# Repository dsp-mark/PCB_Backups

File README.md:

# PCB Storage

Storing KiCAD PCBs here for backup just in case something goes wrong on KiCAD or I need to work on a different computer.

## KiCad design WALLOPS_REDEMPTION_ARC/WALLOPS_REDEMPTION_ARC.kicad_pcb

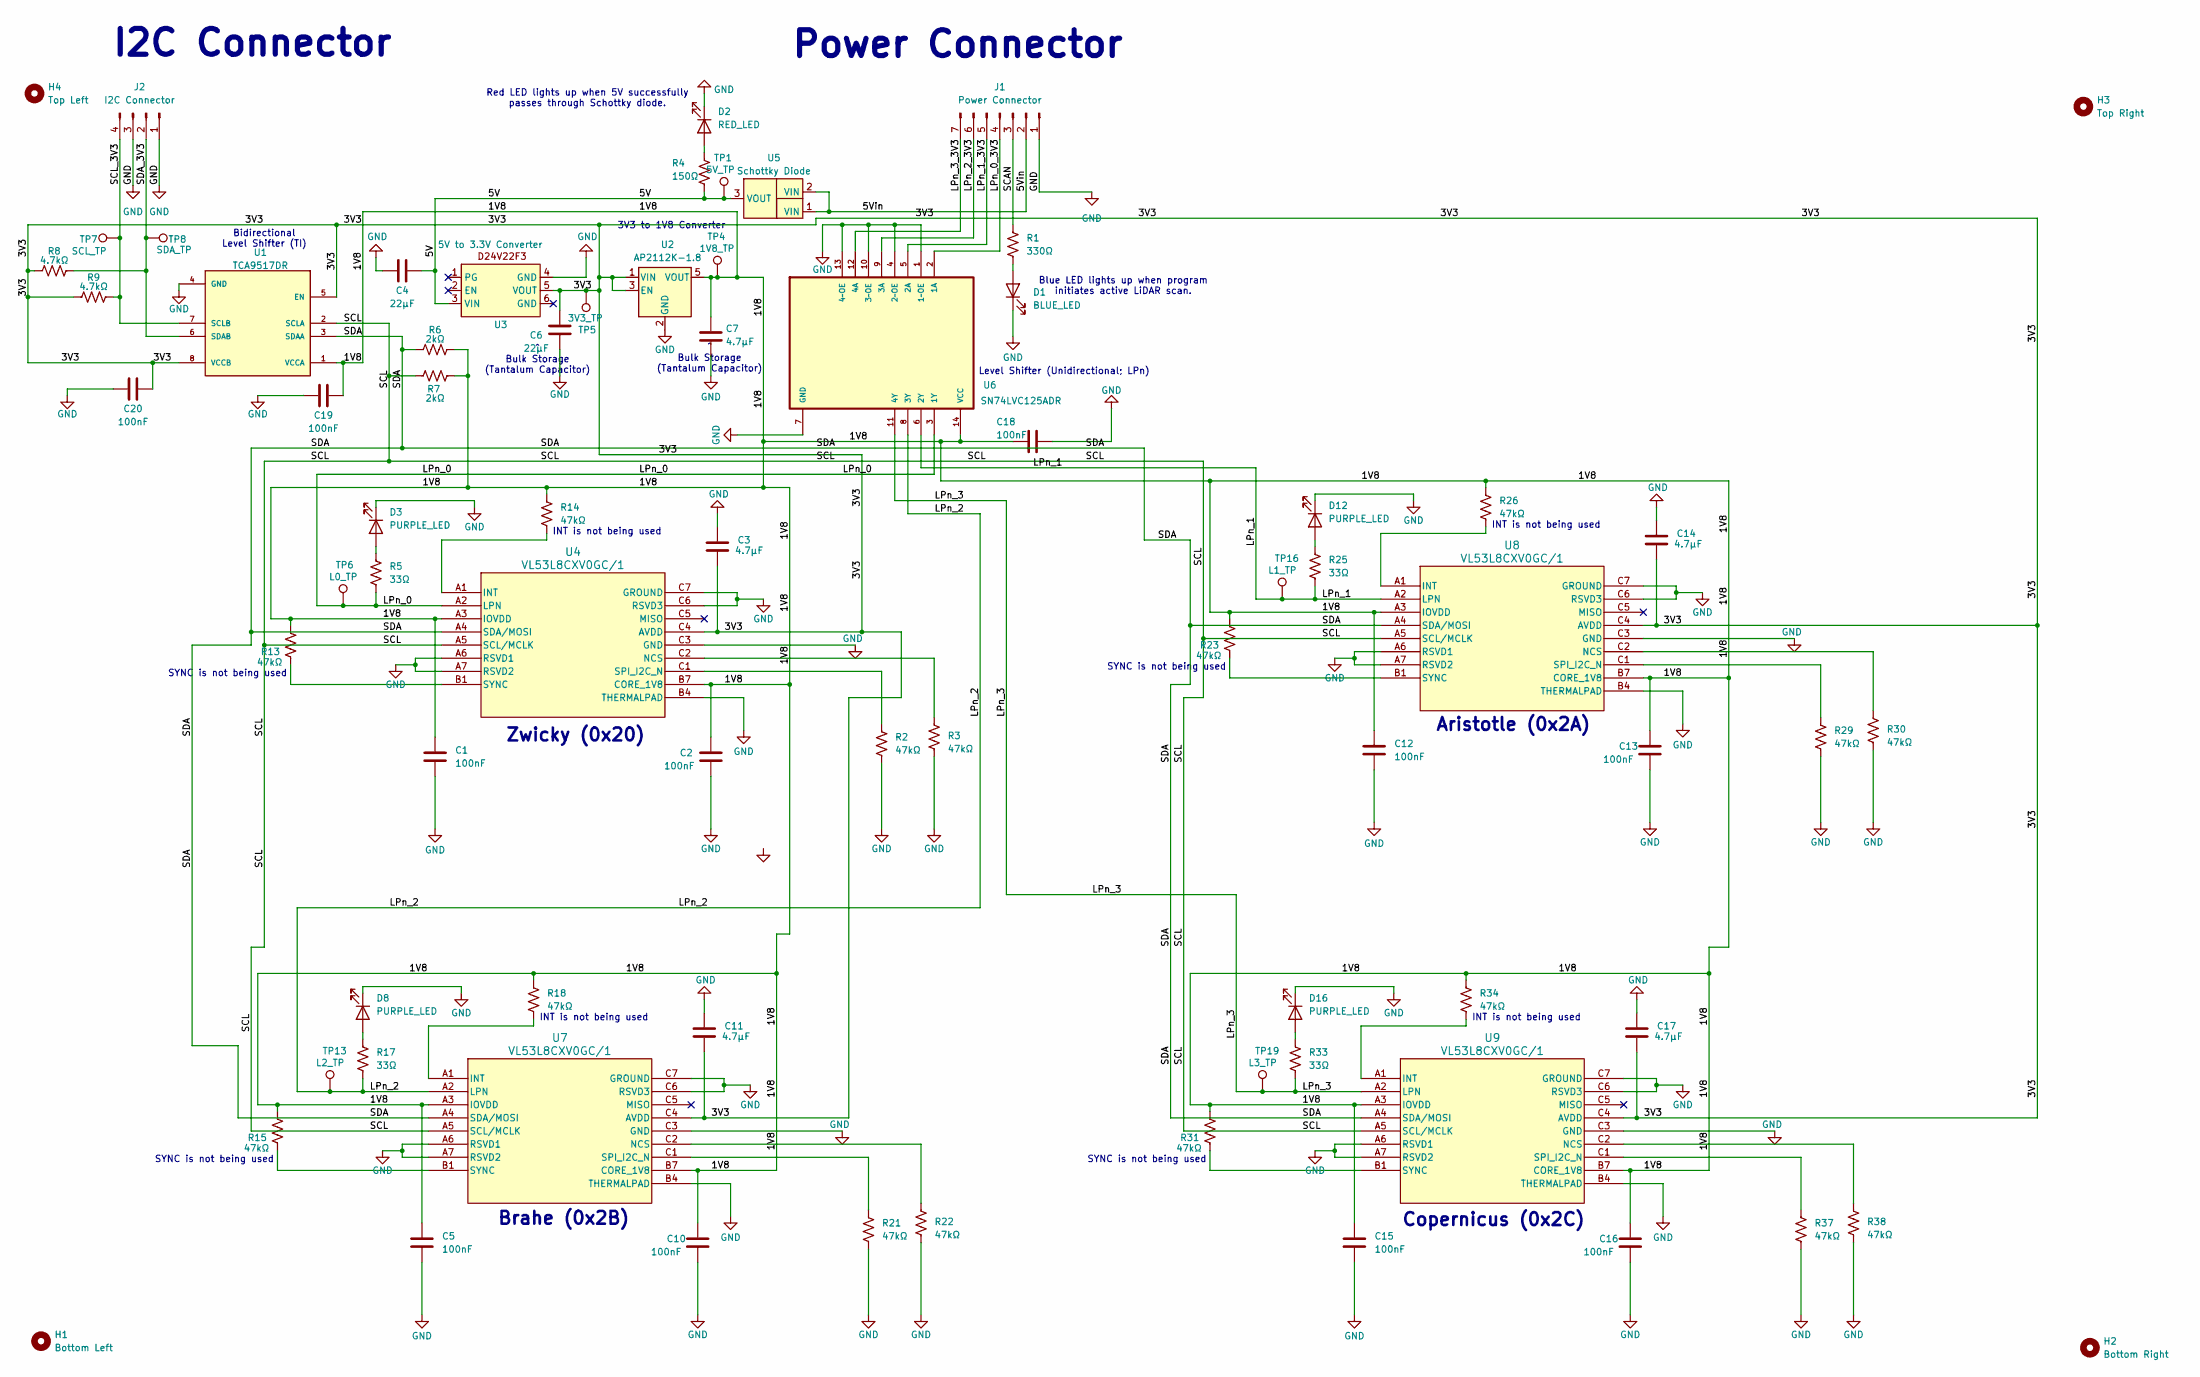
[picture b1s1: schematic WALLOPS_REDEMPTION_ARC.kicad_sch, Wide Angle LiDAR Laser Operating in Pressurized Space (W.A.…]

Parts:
C1, C2, C5, C10, C12, C13, C15, C16, C18, C19, C20: 100nF; C_0805_2012Metric_Pad1.18x1.45mm_HandSolder
C3, C7, C11, C14, C17: 4.7μF; C_0805_2012Metric_Pad1.18x1.45mm_HandSolder
C4, C6: 22μF; C_0805_2012Metric_Pad1.18x1.45mm_HandSolder
D1: BLUE_LED; LED_0805_2012Metric_Pad1.15x1.40mm_HandSolder
D2: RED_LED; LED_0805_2012Metric_Pad1.15x1.40mm_HandSolder
D3, D8, D12, D16: PURPLE_LED; LED_0805_2012Metric_Pad1.15x1.40mm_HandSolder
H1: Bottom Left; MountingHole_3.2mm_M3
H2: Bottom Right; MountingHole_3.2mm_M3
H3: Top Right; MountingHole_3.2mm_M3
H4: Top Left; MountingHole_3.2mm_M3
J1: Power Connector; JST_PH_S7B-PH-K_1x07_P2.00mm_Horizontal
J2: I2C Connector; JST_PH_S4B-PH-K_1x04_P2.00mm_Horizontal
R1: 330Ω; R_0805_2012Metric_Pad1.20x1.40mm_HandSolder
R2, R3, R13, R14, R15, R18, R21, R22, R23, R26, R29, R30, R31, R34, R37, R38: 47kΩ; R_0805_2012Metric_Pad1.20x1.40mm_HandSolder
R4: 150Ω; R_0805_2012Metric_Pad1.20x1.40mm_HandSolder
R5, R17, R25, R33: 33Ω; R_0805_2012Metric_Pad1.20x1.40mm_HandSolder
R6, R7: 2kΩ; R_0805_2012Metric_Pad1.20x1.40mm_HandSolder
R8, R9: 4.7kΩ; R_0805_2012Metric_Pad1.20x1.40mm_HandSolder
TP1: 5V_TP; TestPoint_Pad_D1.0mm
TP4: 1V8_TP; TestPoint_Pad_D1.0mm
TP5: 3V3_TP; TestPoint_Pad_D1.0mm
TP6: L0_TP; TestPoint_Pad_D1.0mm
TP7: SCL_TP; TestPoint_Pad_D1.0mm
TP8: SDA_TP; TestPoint_Pad_D1.0mm
TP13: L2_TP; TestPoint_Pad_D1.0mm
TP16: L1_TP; TestPoint_Pad_D1.0mm
TP19: L3_TP; TestPoint_Pad_D1.0mm
U1: TCA9517DR; SOIC127P599X175-8N; PARTREV D
U2: AP2112K-1.8; SOT-23-5
U3: 5V to 3.3V Converter; D24V22F3
U4, U7, U8, U9: VL53L8CXV0GC/1; vl53l8cx_smd
U5: Schottky Diode; TO-277B
U6: SN74LVC125ADR; SOIC127P600X175-14N

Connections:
/1V8: C1.1, C2.1, C5.1, C7.1, C10.1, C12.1, C13.1, C15.1, C16.1, C18.1, C19.2, R6.2, R7.1, R13.1, R14.1, R15.1, R18.1, R23.1, R26.1, R31.1, R34.1, TP4.1, U1.1 (VCCA), U2.5 (VOUT), U4.A3 (IOVDD), U4.B7 (CORE_1V8), U6.14 (VCC), U7.A3 (IOVDD), U7.B7 (CORE_1V8), U8.A3 (IOVDD), U8.B7 (CORE_1V8), U9.A3 (IOVDD), U9.B7 (CORE_1V8)
/3V3: C3.2, C6.2, C11.2, C14.2, C17.2, C20.2, R8.1, R9.1, TP5.1, U1.5 (EN), U1.8 (VCCB), U2.1 (VIN), U2.3 (EN), U3.5 (VOUT), U4.C4 (AVDD), U7.C4 (AVDD), U8.C4 (AVDD), U9.C4 (AVDD)
/5V: C4.2, R4.2, TP1.1, U3.3 (VIN), U5.3 (VOUT)
/5Vin: J1.2, U5.1 (VIN), U5.2 (VIN)
/LPn_0: R5.2, TP6.1, U4.A2 (LPN), U6.3 (1Y)
/LPn_0_3V3: J1.4, U6.2 (1A)
/LPn_1: R25.2, TP16.1, U6.6 (2Y), U8.A2 (LPN)
/LPn_1_3V3: J1.5, U6.5 (2A)
/LPn_2: R17.2, TP13.1, U6.8 (3Y), U7.A2 (LPN)
/LPn_2_3V3: J1.6, U6.9 (3A)
/LPn_3: R33.2, TP19.1, U6.11 (4Y), U9.A2 (LPN)
/LPn_3_3V3: J1.7, U6.12 (4A)
/SCAN: J1.3, R1.1
/SCL: R7.2, U1.2 (SCLA), U4.A5 (SCL/MCLK), U7.A5 (SCL/MCLK), U8.A5 (SCL/MCLK), U9.A5 (SCL/MCLK)
/SCL_3V3: J2.4, R9.2, TP7.1, U1.7 (SCLB)
/SDA: R6.1, U1.3 (SDAA), U4.A4 (SDA/MOSI), U7.A4 (SDA/MOSI), U8.A4 (SDA/MOSI), U9.A4 (SDA/MOSI)
/SDA_3V3: J2.2, R8.2, TP8.1, U1.6 (SDAB)
GND: C1.2, C2.2, C3.1, C4.1, C5.2, C6.1, C7.2, C10.2, C11.1, C12.2, C13.2, C14.1, C15.2, C16.2, C17.1, C18.2, C19.1, C20.1, D1.1 (K), D2.1 (K), D3.1 (K), D8.1 (K), D12.1 (K), D16.1 (K), J1.1, J2.1, J2.3, R2.2, R3.2, R21.2, R22.2, R29.2, R30.2, R37.2, R38.2, U1.4 (GND), U2.2 (GND), U3.4 (GND), U4.A6 (RSVD1), U4.A7 (RSVD2), U4.B4 (THERMALPAD), U4.C3 (GND), U4.C6 (RSVD3), U4.C7 (GROUND), U6.1 (1~OE), U6.4 (2~OE), U6.7 (GND), U6.10 (3~OE), U6.13 (4~OE), U7.A6 (RSVD1), U7.A7 (RSVD2), U7.B4 (THERMALPAD), U7.C3 (GND), U7.C6 (RSVD3), U7.C7 (GROUND), U8.A6 (RSVD1), U8.A7 (RSVD2), U8.B4 (THERMALPAD), U8.C3 (GND), U8.C6 (RSVD3), U8.C7 (GROUND), U9.A6 (RSVD1), U9.A7 (RSVD2), U9.B4 (THERMALPAD), U9.C3 (GND), U9.C6 (RSVD3), U9.C7 (GROUND)
unnamed: D1.2 (A), R1.2
unnamed: D2.2 (A), R4.1
unnamed: D3.2 (A), R5.1
unnamed: D8.2 (A), R17.1
unnamed: D12.2 (A), R25.1
unnamed: D16.2 (A), R33.1
unnamed: R14.2, U4.A1 (INT)
unnamed: R3.1, U4.C2 (NCS)
unnamed: R2.1, U4.C1 (SPI_I2C_N)
unnamed: R13.2, U4.B1 (SYNC)
unnamed: R18.2, U7.A1 (INT)
unnamed: R22.1, U7.C2 (NCS)
unnamed: R21.1, U7.C1 (SPI_I2C_N)
unnamed: R15.2, U7.B1 (SYNC)
unnamed: R26.2, U8.A1 (INT)
unnamed: R30.1, U8.C2 (NCS)
unnamed: R29.1, U8.C1 (SPI_I2C_N)
unnamed: R23.2, U8.B1 (SYNC)
unnamed: R34.2, U9.A1 (INT)
unnamed: R38.1, U9.C2 (NCS)
unnamed: R37.1, U9.C1 (SPI_I2C_N)
unnamed: R31.2, U9.B1 (SYNC)

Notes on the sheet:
Zwicky (0x20)
INT is not being used
^ Bulk Storage (Tantalum Capacitor)
SYNC is not being used
Brahe (0x2B)
I2C Connector
Bidirectional Level Shifter (TI)
Power Connector
Aristotle (0x2A)
Blue LED lights up when program initiates active LiDAR scan.
3V3 to 1V8 Converter
Red LED lights up when 5V successfully passes through Schottky diode.
Copernicus (0x2C)
Level Shifter (Unidirectional; LPn)

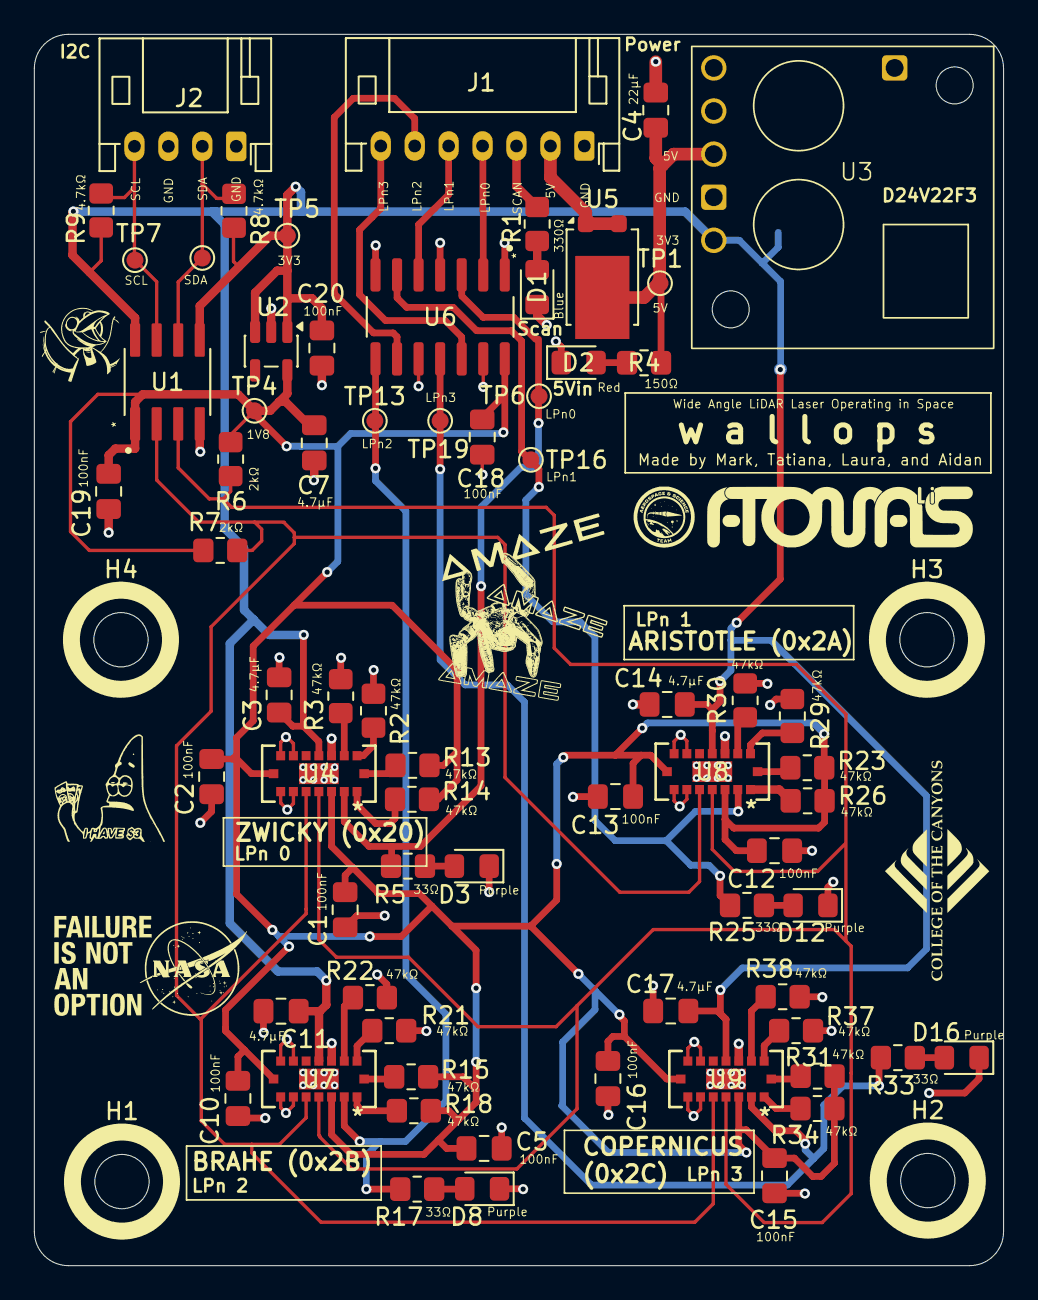
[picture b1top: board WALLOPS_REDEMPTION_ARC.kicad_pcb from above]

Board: 2 copper layers, 57.1 x 72.6 mm, 74 parts (1 on the bottom side), 40 nets.

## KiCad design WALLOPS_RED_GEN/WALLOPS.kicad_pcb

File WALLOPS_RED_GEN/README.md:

# WALLOPS
## Wide Angle LiDAR Laser Operating in Pressurized Space

### Part of College of the Canyons' RockSat 2026 Payload that will be integrated onto a NASA Wallops Sounding Rocket

Connects to a **Raspberry Pi 5** on the Machine Learning Suite board.

Goal is to collect distance data from 4 VL53L8CX 8x8 near infrared sensors to translate into point cloud and recreate pressurized payload on sounding rocket, as well as generate the parts of the payload (e.g. backs of mounted objects) that cannot be observed by the scan using machine learning.

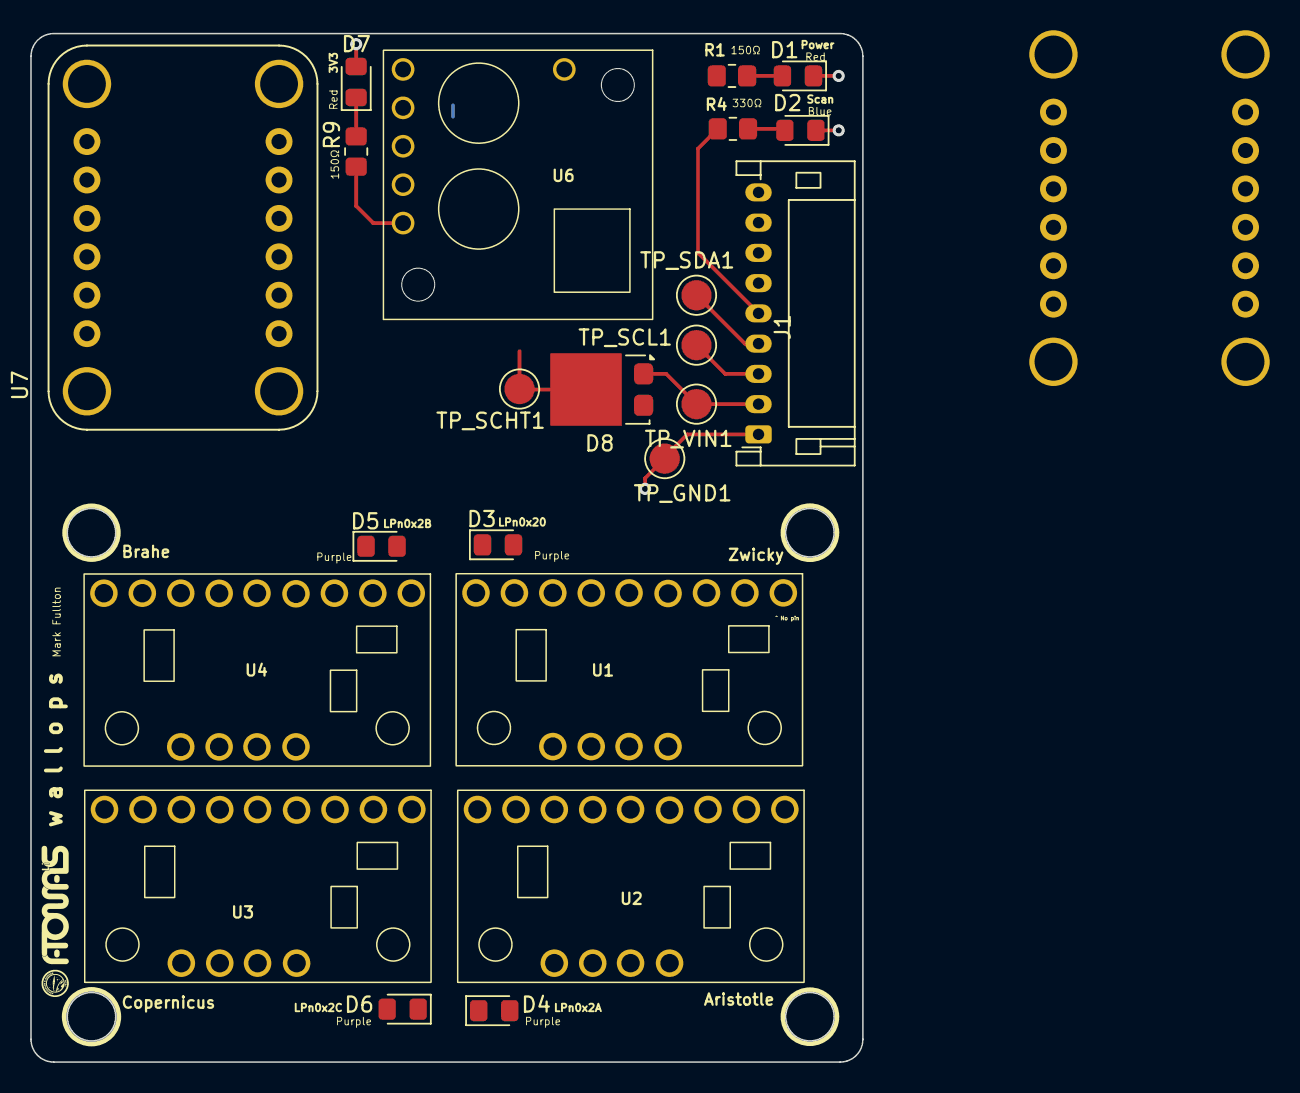
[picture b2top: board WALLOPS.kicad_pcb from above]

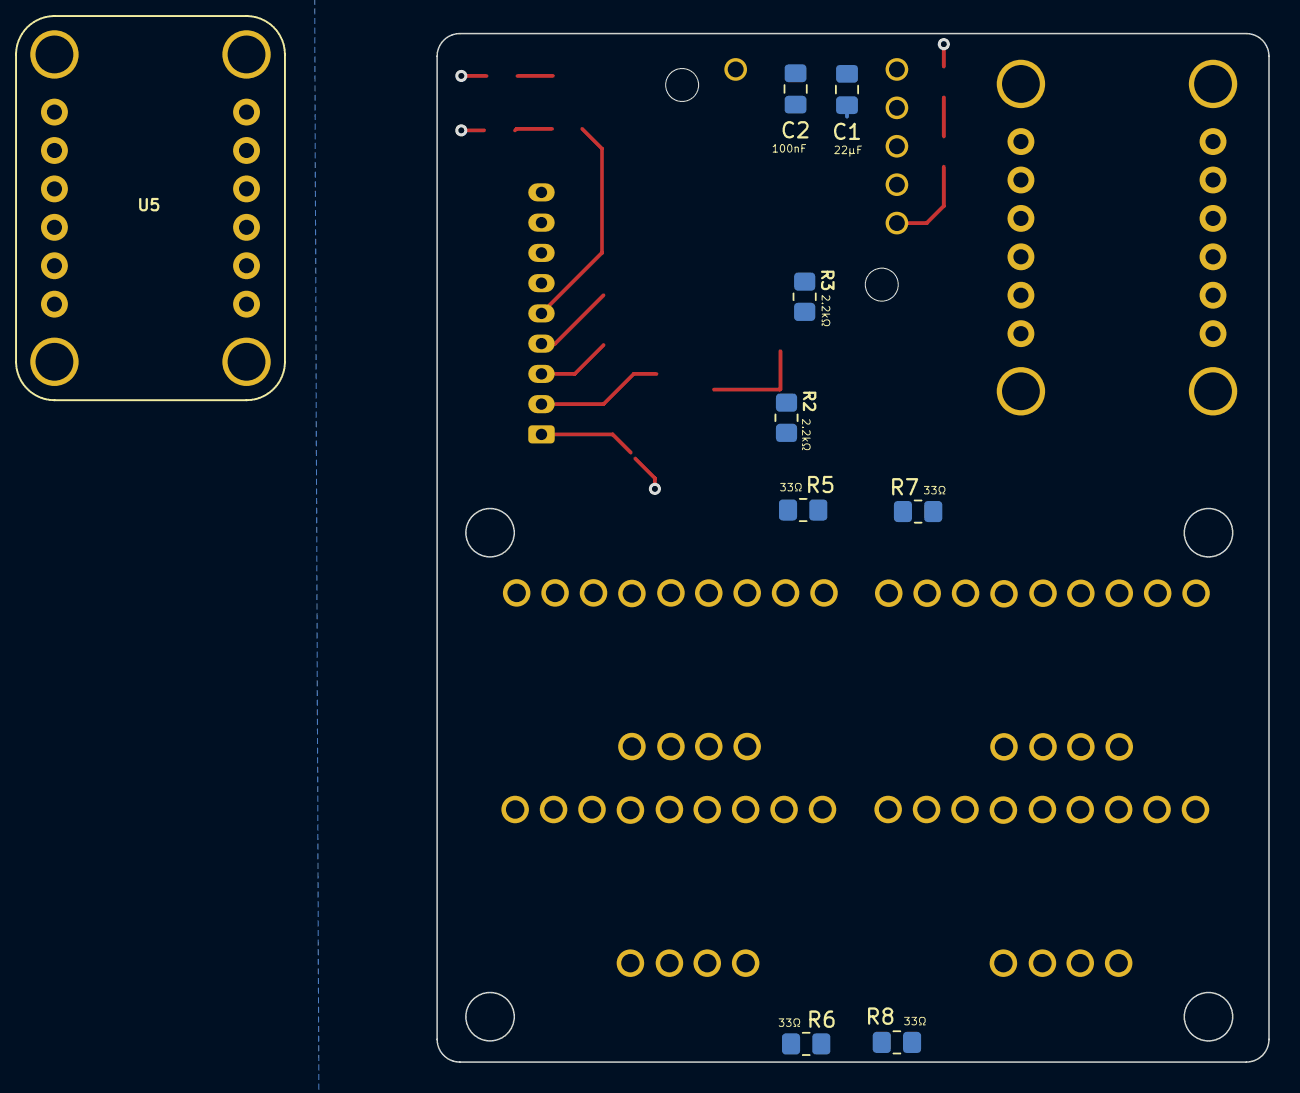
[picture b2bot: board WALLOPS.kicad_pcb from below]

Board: 2 copper layers, 55.0 x 68.0 mm, 32 parts (9 on the bottom side), 18 nets.

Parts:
C1: 22µF; C_0805_2012Metric_Pad1.18x1.45mm_HandSolder
C2: 100nF; C_0805_2012Metric_Pad1.18x1.45mm_HandSolder
D1: RED_LED_5V; LED_0805_2012Metric_Pad1.15x1.40mm_HandSolder
D2: BLUE_LED_3.3V; LED_0805_2012Metric_Pad1.15x1.40mm_HandSolder
D3: LPN0_PURPLE_LED; LED_0805_2012Metric_Pad1.15x1.40mm_HandSolder
D4: LPN1_PURPLE_LED; LED_0805_2012Metric_Pad1.15x1.40mm_HandSolder
D5: LPN2_PURPLE_LED; LED_0805_2012Metric_Pad1.15x1.40mm_HandSolder
D6: LPN3_PURPLE_LED; LED_0805_2012Metric_Pad1.15x1.40mm_HandSolder
D7: RED_LED_3V3; LED_0805_2012Metric_Pad1.15x1.40mm_HandSolder
D8: Schottky; TO-277A
J1: JST-PH 1x9 Connector - WALLOPS to ML Suite; JST_PH_S9B-PH-K_1x09_P2.00mm_Horizontal
R1: 150Ω; R_0805_2012Metric_Pad1.20x1.40mm_HandSolder
R2, R3: 2.2kΩ; R_0805_2012Metric_Pad1.20x1.40mm_HandSolder
R4: 330Ω; R_0805_2012Metric_Pad1.20x1.40mm_HandSolder
R5, R6, R7, R8: 33Ω; R_0805_2012Metric_Pad1.20x1.40mm_HandSolder
R9: 65Ω; R_0805_2012Metric_Pad1.20x1.40mm_HandSolder
TP_GND1: GND_TP; TestPoint_Pad_D2.0mm_With_Tolerance
TP_SCHT1: Post-Schottky Test; TestPoint_Pad_D2.0mm_With_Tolerance
TP_SCL1: SCL_Test; TestPoint_Pad_D2.0mm_With_Tolerance
TP_SDA1: SDA_Test; TestPoint_Pad_D2.0mm_With_Tolerance
TP_VIN1: 5Vin_Test; TestPoint_Pad_D2.0mm_With_Tolerance
U1: VL53L8CX 0 (0x20; Zwicky); VL53L8CX
U2: VL58L8CX 1 (0x2A; Aristotle); VL53L8CX
U3: VL53L8CX 3 (0x2C; Copernicus); VL53L8CX
U4: VL53L8CX 2 (0x2B; Brahe); VL53L8CX
U5: 6DOF IMU (0x69; Sisko); 6DOF IMU
U6: 5V to 3.3V Converter; D24V22F3
U7: LIS3MDL (0x1C; Janeway); L1SEMDL

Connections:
/3.3VOUT: R2.2, R3.1, R9.1, U1.3 (VIN), U2.3 (VIN), U3.3 (VIN), U4.3 (VIN), U6.5 (VOUT), U7.1 (VIN)
/5Vin: C1.2, C2.2, D8.3 (K), R1.2, TP_SCHT1.1, U6.3 (VIN)
/5VinML: D8.1 (A), J1.2, TP_VIN1.1
/LPn_0: J1.6, R5.1, U1.12 (LPn)
/LPn_1: J1.7, R6.1, U2.12 (LPn)
/LPn_2: J1.8, R7.1, U4.12 (LPn)
/LPn_3: J1.9, R8.1, U3.12 (LPn)
/SCAN_LED: J1.5, R4.1
/SCL: J1.3, R2.1, TP_SCL1.1, U1.6 (SCL), U2.6 (SCL), U3.6 (SCL), U4.6 (SCL), U7.4 (SCL)
/SDA: J1.4, R3.2, TP_SDA1.1, U1.5 (SDA), U2.5 (SDA), U3.5 (SDA), U4.5 (SDA), U7.5 (SDA)
GND: C1.1, C2.1, D1.1 (K), D2.1 (K), D3.2 (A), D4.2 (A), D5.2 (A), D6.2 (A), D7.2 (A), J1.1, TP_GND1.1, U1.4 (GND), U1.10 (GND), U1.11 (SPI/I2C), U2.4 (GND), U2.10 (GND), U2.11 (SPI/I2C), U3.4 (GND), U3.10 (GND), U3.11 (SPI/I2C), U4.4 (GND), U4.10 (GND), U4.11 (SPI/I2C), U6.4 (GND), U7.3 (GND)
unnamed: D1.2 (A), R1.1
unnamed: D2.2 (A), R4.2
unnamed: D3.1 (K), R5.2
unnamed: D4.1 (K), R6.2
unnamed: D5.1 (K), R7.2
unnamed: D6.1 (K), R8.2
unnamed: D7.1 (K), R9.2

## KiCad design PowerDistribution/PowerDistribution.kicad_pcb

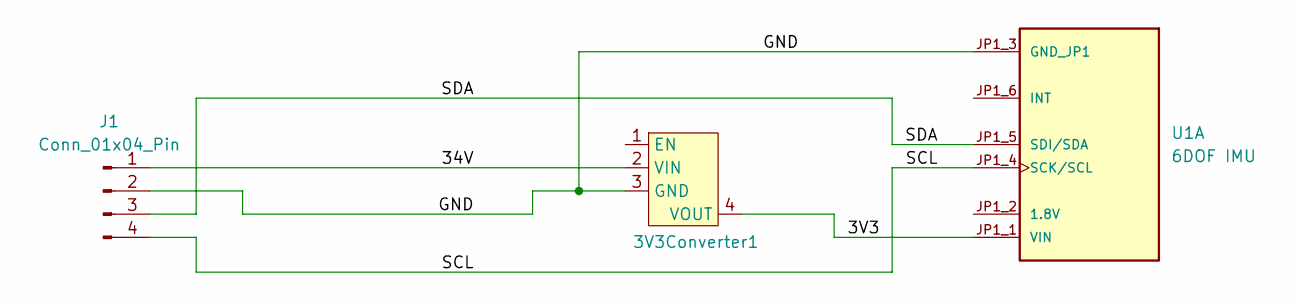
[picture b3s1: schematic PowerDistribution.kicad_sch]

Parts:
3V3Converter1: APM81815
J1: Conn_01x04_Pin; JST_PH_B4B-PH-K_1x04_P2.00mm_Vertical
U1: 6DOF IMU; PARTREV N/A

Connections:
/3V3: 3V3Converter1.4 (VOUT), U1.JP1_1 (VIN)
/34V: 3V3Converter1.2 (VIN), J1.1
/GND: 3V3Converter1.3 (GND), J1.2, U1.JP1_3 (GND_JP1)
/SCL: J1.4, U1.JP1_4 (SCK/SCL)
/SDA: J1.3, U1.JP1_5 (SDI/SDA)

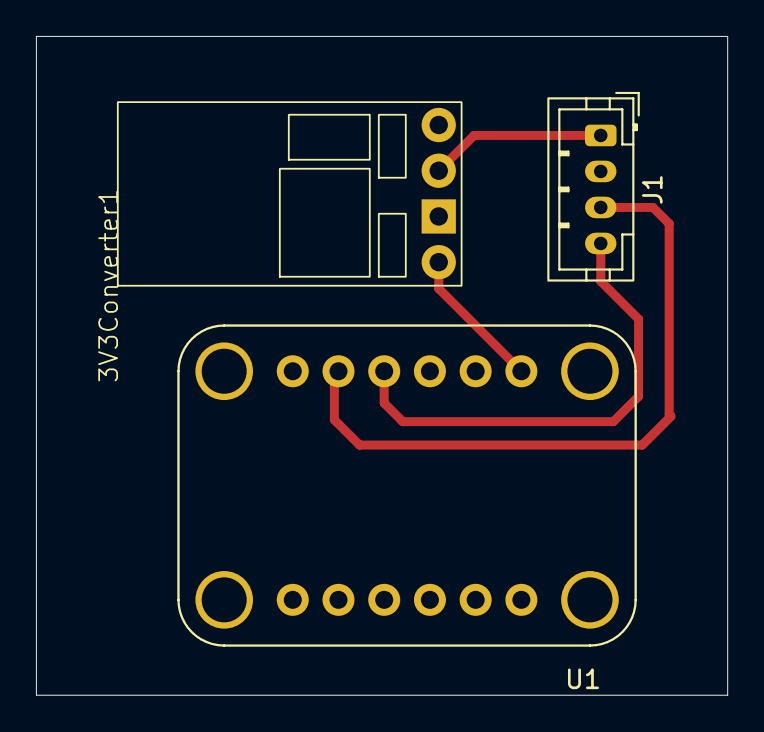
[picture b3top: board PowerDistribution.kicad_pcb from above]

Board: 2 copper layers, 38.4 x 36.6 mm, 3 parts (0 on the bottom side), 5 nets.

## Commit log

2026-01-16 Added Initial Wallops PCB
2026-01-16 Added updated schematics for WALLOPS
2026-01-18 Hooked up AVDD to LPn
2026-01-20 Added new 1x9 JST-PH vertical connector from WALLOPS to ML Suite
2026-01-22 Updated schematic and PCB; added symbol, dimensions, and footprint for Pololu VL53L8CX carrier board
2026-01-22 Added footprint and readme for WALLOPS
2026-01-22 Updated pcb layout and renamed WALLOPS.md to README.md
2026-01-29 Swapped out sch diode with P-MOSFET to fix backflow on 5VIN
2026-01-29 Removed extraneous test pins
2026-01-29 Finished first draft of wallops pcb layout
2026-02-05 Added updated Wallops PCB + schematic
2026-02-05 Added updated WALLOPS PCB
2026-02-07 Updated PCB
2026-02-07 Reduced PCB size
2026-02-07 Reduced size in WALLOPS
2026-02-11 Reduced size of PCB
2026-02-11 Added silkscreen to WALLOPS pcb
2026-02-11 Added symbols for WALLOPS version 12
2026-02-12 Added teardrops to WALLOPS LiDAR PCB
2026-02-14 Added updated WALLOPS with 3D components
2026-02-14 Updated readme with WALLOPS v2
2026-02-28 Updated capacitors to filter noise and added magnetometer
2026-02-28 Added Magnetometer to schematic
2026-03-02 Added individual TOF LPn pins to WALLOPS PCB
2026-03-02 Fixed WALLOPS JST-PH footprint; switched 0603 LEDs back to 0805
2026-03-03 Added ATMOLiS logo to WALLOPS PCB
2026-03-06 Added WALLOPS PCB version 3 (Blue Gen)
2026-03-06 Cleaned up WALLOPS PCB and added silkscreen
2026-03-12 Added updates to WALLOPS and schematic for ML Suite Steppers
2026-03-12 Added stepper driver schematic
2026-03-24 Added replacement 3V3 files for Power Distribution board
2026-04-05 Added start to 555 circuit
2026-04-05 Updated 555 circuit schematic
2026-04-05 Added logic inverter to the 555 timer to toggle on the battery draw to ML system
2026-04-05 Added schematic for 555 timers
2026-04-07 Added ml power timer breadboard schematic
2026-04-07 Updated schematic for breadboard
2026-04-11 Revising ML battery power logic schematic
2026-04-12 Added updated ML power logic timer
2026-04-20 Added Red Generation PCB
2026-05-28 Added current WALLOPS PCB (Redemption)
2026-05-28 Added current schematic for WALLOPS
2026-05-30 Updated schematic
2026-05-30 Added base PCB dimensions
2026-05-31 Added passives for power side of PCB
2026-06-04 Updated Wallops Redemption ARC
